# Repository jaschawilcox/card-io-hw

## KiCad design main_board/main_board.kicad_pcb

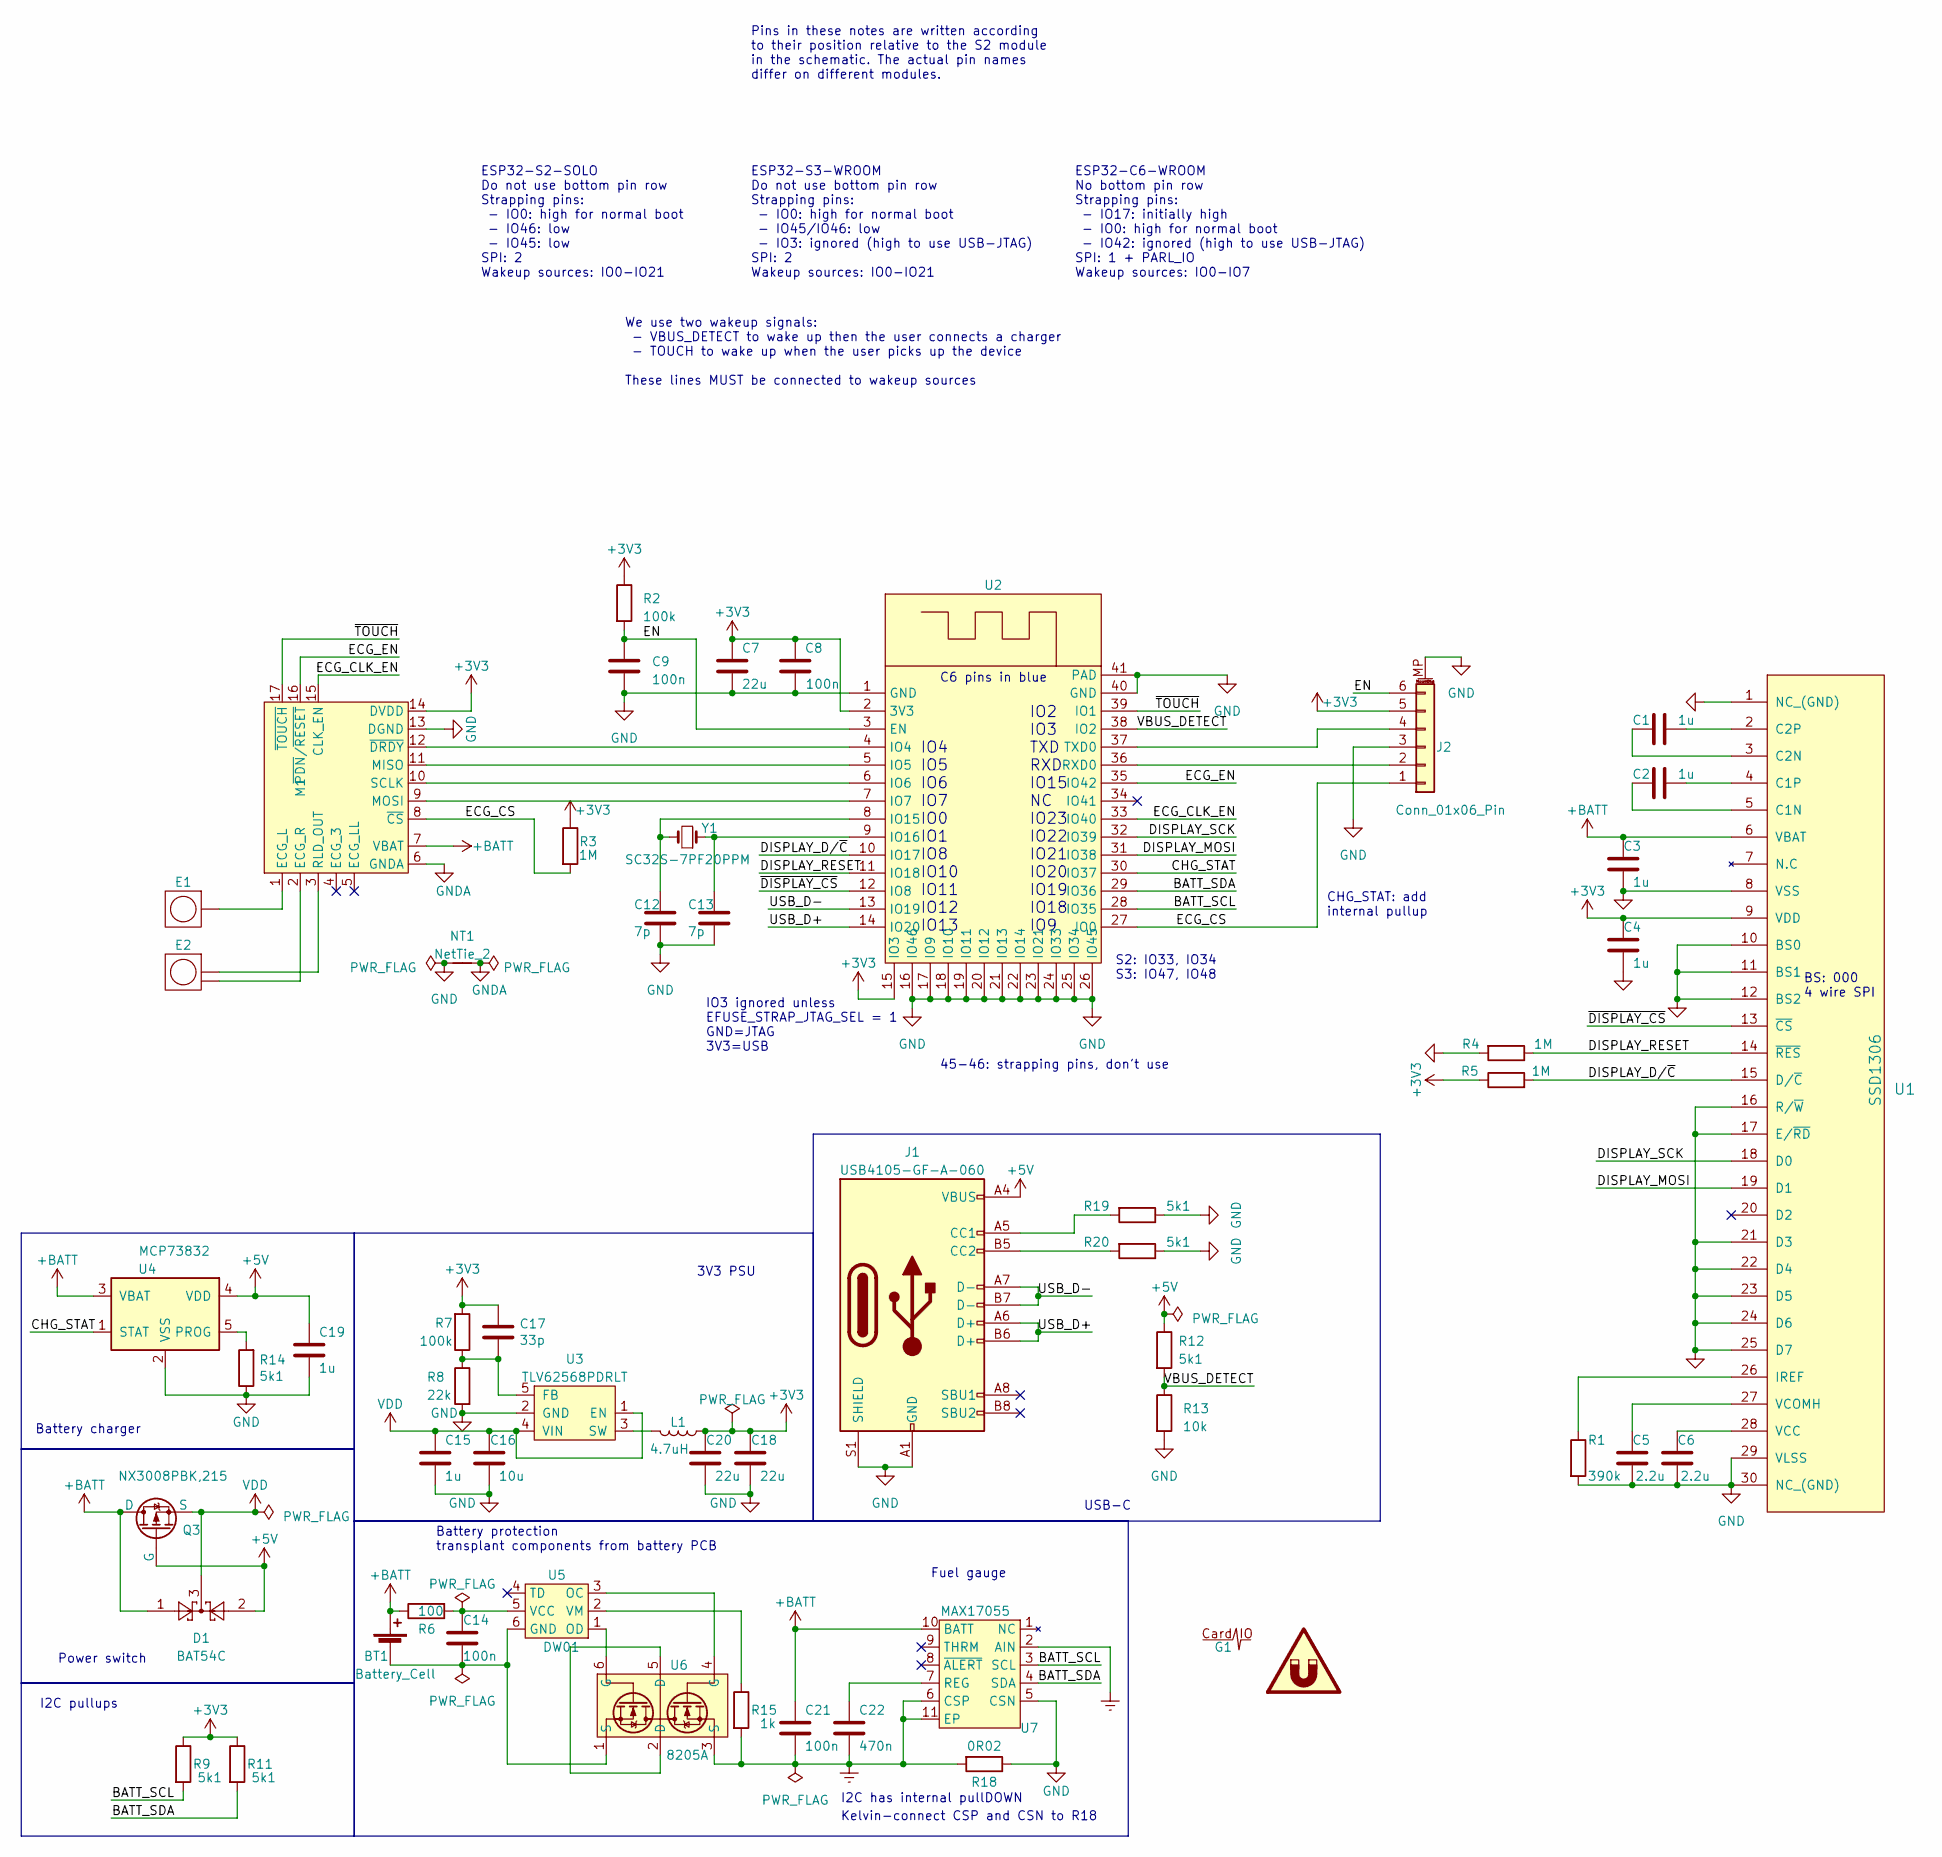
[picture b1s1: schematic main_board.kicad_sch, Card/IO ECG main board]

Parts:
BT1: Battery_Cell; Battery_transplant
C1, C2, C3, C4, C15, C19: 1u; C_0603_1608Metric; MPN CC0603KRX7R6BB105; LCSC Part # C113807
C5, C6: 2.2u; C_0603_1608Metric; MPN CC0603ZRY5V6BB225; LCSC Part # C106849
C7, C18, C20: 22u; C_0805_2012Metric; MPN CC0603MRX5R6BB226; LCSC Part # C109447
C8, C9, C14, C21: 100n; C_0603_1608Metric; MPN AC0603KRX7R0BB104; LCSC Part # C408909
C12, C13: 7p; C_0603_1608Metric; MPN CC0603DRNPO9BN7R0; LCSC Part # C513583
C16: 10u; C_0603_1608Metric; MPN JMK107ABJ106MA-T; LCSC Part # C268008
C17: 33p; C_0603_1608Metric; MPN CC0603JRNPO9BN330; LCSC Part # C107047
C22: 470n; C_0603_1608Metric; MPN CC0603JRX7R7BB474; LCSC Part # C519558
D1: BAT54C; SOT-23; MPN BAT54C; LCSC Part # C171429
E1: Electrode
E2: SplitElectrode
G1: logo
J1: USB4105-GF-A-060; USB_C_Receptacle_GCT_USB4105-xx-A_16P_TopMnt_Horizontal; MPN USB-TYPE-C-018; LCSC Part # C2927038
J2: Conn_01x06_Pin; Molex_Pico-Clasp_501331-0607_1x06-1MP_P1.00mm_Vertical; MPN 5013310607; LCSC Part # C587861
L1: 4.7uH; TYA40124R7M-10; MPN TYA40124R7M-10; LCSC Part # C2649049
M1: ECG-module_1lead
NT1: NetTie_2; NetTie-2_SMD_Pad2.0mm
Q3: NX3008PBK,215; SOT-23; MPN NX3008PBK,215; LCSC Part # C131670
QR1: SYM_Magnet_Large; website-qr
R1: 390k; R_0603_1608Metric; MPN RC0603FR-07390KL; LCSC Part # C137735
R2, R7: 100k; R_0603_1608Metric; MPN RC0603JR-07100KL; LCSC Part # C100048
R3, R4, R5: 1M; R_0603_1608Metric; MPN RT0603DRD071ML; LCSC Part # C482623
R6: 100; R_0603_1608Metric; MPN RT0603BRD07100RL; LCSC Part # C122970
R8: 22k; R_0603_1608Metric; MPN RC0603FR-0722KL; LCSC Part # C114065
R9, R11, R12, R14, R19, R20: 5k1; R_0603_1608Metric; MPN RT0603FRE075K1L; LCSC Part # C706184
R13: 10k; R_0603_1608Metric; MPN RT0603BRD0710KL; LCSC Part # C95204
R15: 1k; R_0603_1608Metric; MPN RT0603FRE071KL; LCSC Part # C375503
R18: 0R02; R_0603_1608Metric; MPN PE0603FRF570R02L; LCSC Part # C1730619
U1: SSD1306
U2: ESP32-S2-SOLO; MPN ESP32-S2-SOLO-2-N4; LCSC Part # C3040594
U3: TLV62568PDRLT; SOT-23-5; MPN TLV62568PDRLT; LCSC Part # C2071727
U4: MCP73832; SOT-23-5; MPN MCP73832T-2ACI/OT; LCSC Part # C38066
U5: DW01; SOT-23-6; MPN DW01; LCSC Part # C917079
U6: 8205A; SOT-23-6; MPN 8205A; LCSC Part # C2762931
U7: MAX17055; MPN MAX17055ETB+; LCSC Part # C402925
Y1: SC32S-7PF20PPM; Crystal_SMD_MicroCrystal_CC7V-T1A-2Pin_3.2x1.5mm; MPN SC32S-7PF20PPM; LCSC Part # C5452100

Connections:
+3V3: C4.2, C7.1, C8.1, C17.1, C18.1, C20.1, J2.5, L1.1, M1.14 (DVDD), R2.1, R3.1, R5.1, R7.2, R9.1, R11.1, U1.9 (VDD), U2.2 (3V3), U2.15 (IO3)
+5V: C19.1, D1.2, J1.A4 (VBUS), J1.A9 (VBUS), J1.B4 (VBUS), J1.B9 (VBUS), Q3.1 (G), R12.1, U4.4 (VDD)
+BATT: BT1.1 (+), C3.2, C21.1, D1.1, M1.7 (VBAT), Q3.3 (D), R6.1, U1.6 (VBAT), U4.3 (VBAT), U7.10 (BATT)
/BATT_SCL: R9.2, U2.28 (IO35), U7.3 (SCL)
/BATT_SDA: R11.2, U2.29 (IO36), U7.4 (SDA)
/CHG_STAT: U2.30 (IO37), U4.1 (STAT)
/DISPLAY_D/~C: R5.2, U1.15 (D/~C), U2.10 (IO17)
/DISPLAY_MOSI: U1.19 (D1), U2.31 (IO38)
/DISPLAY_RESET: R4.1, U1.14 (~RES), U2.11 (IO18)
/DISPLAY_SCK: U1.18 (D0), U2.32 (IO39)
/ECG_CLK_EN: M1.15 (CLK_EN), U2.33 (IO40)
/ECG_CS: J2.1, M1.8 (~CS), R3.2, U2.27 (IO0)
/ECG_EN: M1.16 (~PDN/~RESET), U2.35 (IO42)
/EN: C9.1, J2.6, R2.2, U2.3 (EN)
/USB_D+: J1.A6 (D+), J1.B6 (D+), U2.14 (IO20)
/USB_D-: J1.A7 (D-), J1.B7 (D-), U2.13 (IO19)
/VBUS_DETECT: R12.2, R13.1, U2.38 (IO2)
/~DISPLAY_CS: U1.13 (~CS), U2.12 (IO8)
/~TOUCH: M1.17 (~TOUCH), U2.39 (IO1)
Earth: C21.2, C22.2, R15.2, R18.2, U6.3 (S), U7.2 (AIN), U7.6 (CSP), U7.11 (EP)
GND: C3.1, C4.1, C5.1, C6.1, C7.2, C8.2, C9.2, C12.1, C13.1, C15.2, C16.2, C18.2, C19.2, C20.2, J1.A1 (GND), J1.A12 (GND), J1.B1 (GND), J1.B12 (GND), J1.S1 (SHIELD), J2.3, J2.MP (MountPin), M1.13 (DGND), NT1.1, R1.2, R4.2, R8.2, R13.2, R14.1, R18.1, R19.1, R20.1, U1.1 (NC_(GND)), U1.8 (VSS), U1.10 (BS0), U1.11 (BS1), U1.12 (BS2), U1.16 (R/~W), U1.17 (E/~RD), U1.21 (D3), U1.22 (D4), U1.23 (D5), U1.24 (D6), U1.25 (D7), U1.29 (VLSS), U1.30 (NC_(GND)), U2.1 (GND), U2.16 (IO46), U2.17 (IO9), U2.18 (IO10), U2.19 (IO11), U2.20 (IO12), U2.21 (IO13), U2.22 (IO14), U2.23 (IO21), U2.24 (IO33), U2.25 (IO34), U2.26 (IO45), U2.40 (GND), U2.41 (PAD), U3.2 (GND), U4.2 (VSS), U7.5 (CSN)
GNDA: M1.6 (GNDA), NT1.2
unnamed: BT1.2 (-), C14.2, U5.6 (GND), U6.1 (S)
unnamed: J1.A5 (CC1), R19.2
unnamed: J1.B5 (CC2), R20.2
unnamed: J2.2, U2.36 (RXD0)
unnamed: J2.4, U2.37 (TXD0)
unnamed: E1.1, M1.1 (ECG_L)
unnamed: E2.2, M1.2 (ECG_R)
unnamed: M1.11 (MISO), U2.5 (IO5)
unnamed: M1.9 (MOSI), U2.7 (IO7)
unnamed: E2.1, M1.3 (RLD_OUT)
unnamed: M1.10 (SCLK), U2.6 (IO6)
unnamed: M1.12 (~DRDY), U2.4 (IO4)
unnamed: C2.1, U1.5 (C1N)
unnamed: C2.2, U1.4 (C1P)
unnamed: C1.1, U1.3 (C2N)
unnamed: C1.2, U1.2 (C2P)
unnamed: R1.1, U1.26 (IREF)
unnamed: C6.2, U1.28 (VCC)
unnamed: C5.2, U1.27 (VCOMH)
unnamed: C12.2, U2.8 (IO15), Y1.2
unnamed: C13.2, U2.9 (IO16), Y1.1
unnamed: C17.2, R7.1, R8.1, U3.5 (FB)
unnamed: L1.2, U3.3 (SW)
unnamed: R14.2, U4.5 (PROG)
unnamed: U5.3 (OC), U6.4 (G)
unnamed: U5.1 (OD), U6.6 (G)
unnamed: C14.1, R6.2, U5.5 (VCC)
unnamed: R15.1, U5.2 (VM)
unnamed: U6.2 (D), U6.5 (D)
unnamed: C22.1, U7.7 (REG)
VDD: C15.1, C16.1, D1.3, Q3.2 (S), U3.1 (EN), U3.4 (VIN)

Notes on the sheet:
IO2 IO3 TXD RXD IO15 NC IO23 IO22 IO21 IO20 IO19 IO18 IO9
IO4 IO5 IO6 IO7 IO0 IO1 IO8 IO10 IO11 IO12 IO13
We use two wakeup signals: - VBUS_DETECT to wake up then the user connects a charger - TOUCH to wake up when the user picks up the device These lines MUST be connected to wakeup sources
C6 pins in blue
USB-C
ESP32-C6-WROOM No bottom pin row Strapping pins: - IO17: initially high - IO0: high for normal boot - IO42: ignored (high to use USB-JTAG) SPI: 1 + PARL_IO Wakeup sources: IO0-IO7
Kelvin-connect CSP and CSN to R18
ESP32-S3-WROOM Do not use bottom pin row Strapping pins: - IO0: high for normal boot - IO45/IO46: low - IO3: ignored (high to use USB-JTAG) SPI: 2 Wakeup sources: IO0-IO21
Battery charger
ESP32-S2-SOLO Do not use bottom pin row Strapping pins: - IO0: high for normal boot - IO46: low - IO45: low SPI: 2 Wakeup sources: IO0-IO21
CHG_STAT: add internal pullup
Pins in these notes are written according to their position relative to the S2 module in the schematic. The actual pin names differ on different modules.
Fuel gauge
3V3 PSU
BS: 000 4 wire SPI
45-46: strapping pins, don't use
I2C has internal pullDOWN
Battery protection transplant components from battery PCB
S2: IO33, IO34 S3: IO47, IO48
I2C pullups
IO3 ignored unless EFUSE_STRAP_JTAG_SEL = 1 GND=JTAG 3V3=USB
Power switch

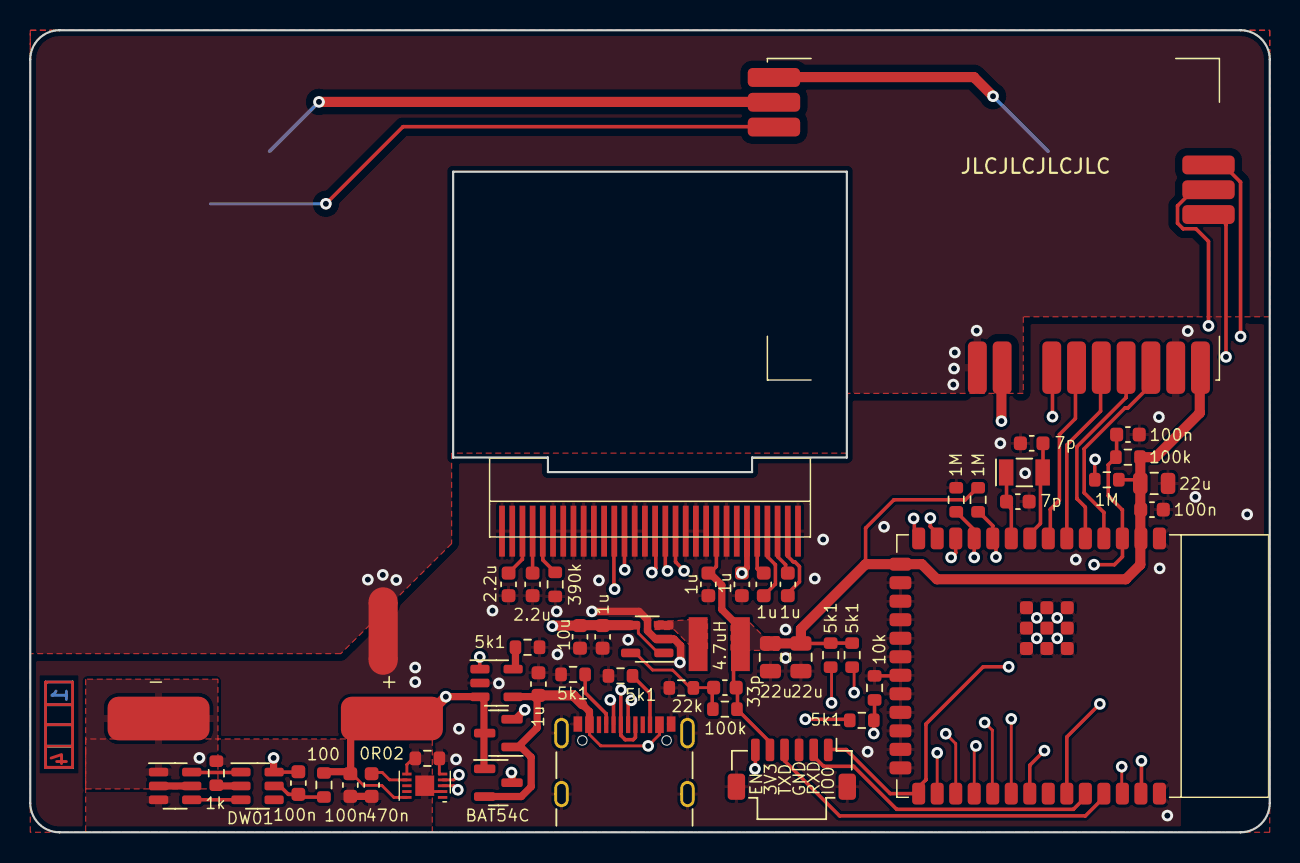
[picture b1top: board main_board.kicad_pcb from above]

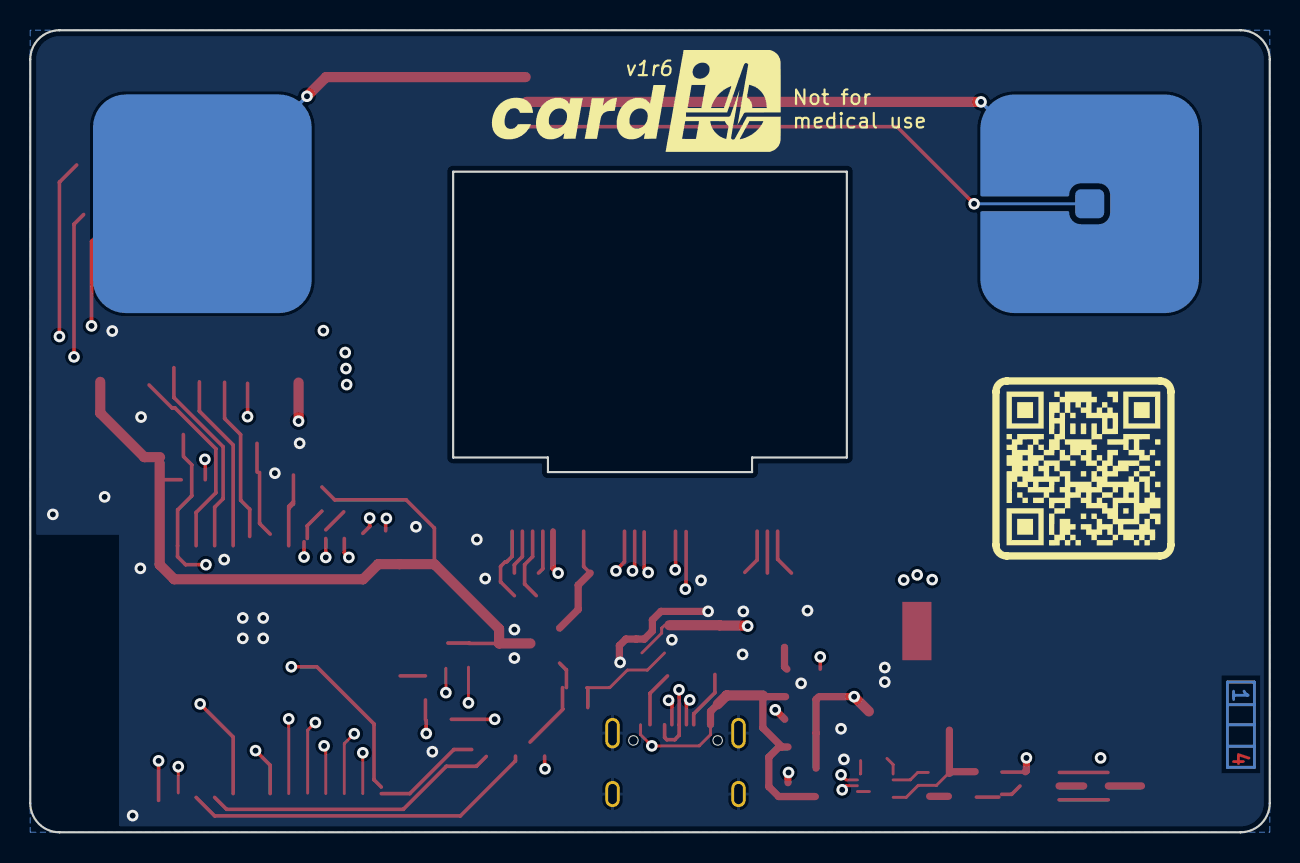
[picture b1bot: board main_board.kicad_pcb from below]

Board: 4 copper layers, 85.0 x 55.0 mm, 57 parts (4 on the bottom side), 53 nets.

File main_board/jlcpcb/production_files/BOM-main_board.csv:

Comment,Designator,Footprint,LCSC
1M,"R3,R4,R5",R_0603_1608Metric,C482623
5k1,R14,R_0603_1608Metric,
8205A,U6,SOT-23-6,
22u,C7,C_0805_2012Metric,
100,R6,R_0603_1608Metric,
470n,C22,C_0603_1608Metric,
100k,R2,R_0603_1608Metric,
TLV62568PDRLT,U3,SOT-23-5,
22k,R8,R_0603_1608Metric,
100k,R7,R_0603_1608Metric,
100n,C14,C_0603_1608Metric,
100n,C21,C_0603_1608Metric,
100n,C8,C_0603_1608Metric,
1u,C2,C_0603_1608Metric,
33p,C17,C_0603_1608Metric,
5k1,R9,R_0603_1608Metric,
ESP32-S2-SOLO,U2,ESP32-S2-SOLO,
SSD1306,U1,SSD1306,
7p,C13,C_0603_1608Metric,
1u,C15,C_0603_1608Metric,
10u,C16,C_0603_1608Metric,
1u,C1,C_0603_1608Metric,
MAX17055,U7,MAX17055,
Conn_01x06_Pin,J2,Molex_Pico-Clasp_501331-0607_1x06-1MP_P1.00mm_Vertical,
1u,C3,C_0603_1608Metric,
100n,C9,C_0603_1608Metric,
Battery_Cell,BT1,Battery_transplant,
2.2u,C6,C_0603_1608Metric,
5k1,R19,R_0603_1608Metric,
MCP73832,U4,SOT-23-5,
1u,C4,C_0603_1608Metric,
390k,R1,R_0603_1608Metric,
SC32S-7PF20PPM,Y1,Crystal_SMD_MicroCrystal_CC7V-T1A-2Pin_3.2x1.5mm,
2.2u,C5,C_0603_1608Metric,
4.7uH,L1,TYA40124R7M-10,
5k1,R12,R_0603_1608Metric,
5k1,R20,R_0603_1608Metric,
5k1,R11,R_0603_1608Metric,
"NX3008PBK,215",Q3,SOT-23,
1u,C19,C_0603_1608Metric,
1k,R15,R_0603_1608Metric,
22u,C20,C_0805_2012Metric,
~,M1,ECG-module_1lead,
0R02,R18,R_0603_1608Metric,
7p,C12,C_0603_1608Metric,
22u,C18,C_0805_2012Metric,
10k,R13,R_0603_1608Metric,
USB4105-GF-A-060,J1,USB_C_Receptacle_GCT_USB4105-xx-A_16P_TopMnt_Horizontal,
DW01,U5,SOT-23-6,
BAT54C,D1,SOT-23,

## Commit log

2024-02-07 Cleanup BOM
2024-02-07 fix package issue on bom
2024-05-23 1st prod attempt
    ¯\_(ツ)_/¯
2024-06-06 add frontend bom, kicad version bump
